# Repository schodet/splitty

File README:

Splitty
=======

This is a split ergonomic keyboard based on the Ergodox layout without the
thumb cluster. It uses 32 keys per sides with Cherry MX compatibles switches,
thirty 1u and two vertical 1.5u caps.

The controller is integrated in order to make the keyboard as slim as
possible.

It connects to the computer using a micro-B USB. Both sides are connected
together also using micro-B USB. Any connection mistake should not break
anything and the keyboard supports hot plugging.

License
------- 

Copyright (C) 2018 Nicolas Schodet

Permission is hereby granted, free of charge, to any person obtaining a copy
of this software and associated documentation files (the "Software"), to deal
in the Software without restriction, including without limitation the rights
to use, copy, modify, merge, publish, distribute, sublicense, and/or sell
copies of the Software, and to permit persons to whom the Software is
furnished to do so, subject to the following conditions:

The above copyright notice and this permission notice shall be included in all
copies or substantial portions of the Software.

THE SOFTWARE IS PROVIDED "AS IS", WITHOUT WARRANTY OF ANY KIND, EXPRESS OR
IMPLIED, INCLUDING BUT NOT LIMITED TO THE WARRANTIES OF MERCHANTABILITY,
FITNESS FOR A PARTICULAR PURPOSE AND NONINFRINGEMENT. IN NO EVENT SHALL THE
AUTHORS OR COPYRIGHT HOLDERS BE LIABLE FOR ANY CLAIM, DAMAGES OR OTHER
LIABILITY, WHETHER IN AN ACTION OF CONTRACT, TORT OR OTHERWISE, ARISING FROM,
OUT OF OR IN CONNECTION WITH THE SOFTWARE OR THE USE OR OTHER DEALINGS IN THE
SOFTWARE.

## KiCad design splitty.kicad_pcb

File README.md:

Splitty
=======

[More pictures](gallery.md)

This is a split ergonomic keyboard based on the Ergodox layout without the
thumb cluster. It uses 32 keys per sides with Cherry MX compatibles switches,
thirty 1u and two vertical 1.5u caps.

The controller is integrated in order to make the keyboard as slim as
possible.

It connects to the computer using a micro-B USB. Both sides are connected
together also using micro-B USB. Any connection mistake should not break
anything and the keyboard supports hot plugging.

BOM
---

All prices in euro.

Here is what is needed for one half, with references at Farnell and LCSC for
some parts.

| Quantity | Designator   | Description                              | Farnell   | Price | Total | LCSC    | Price  | Total |
| -------: | ------------ | ---------------------------------------- | --------: | ----: | ----: | ------: | -----: | ----: |
|       32 | SW0-38       | Cherry MX switches                       |           |       |       |         |        |       |
|        3 | C1, C11, C12 | Capacitor 0603 1μF >6V X7R               |   2346895 | 0.055 | 0.165 |  C93816 | 0.0172 | 0.052 |
|        2 | C3, C4       | Capacitor 0603 22pF >6V C0G/NP0          |   xxxxxxx | xxxxx | xxxxx | C106245 | 0.0084 | 0.017 |
|        6 | C5-10        | Capacitor 0603 100nF >6V X7R             |   2320803 | 0.037 | 0.222 | C187860 | 0.0231 | 0.139 |
|       32 | D0-38        | Diode SOD-123                            |   2760402 | 0.079 | 2.528 |  C83528 | 0.0091 | 0.291 |
|        2 | J1,J2        | Connector USB Micro-B Würth 629105150521 |   2470822 | 1.360 | 2.720 |         |        |       |
|        2 | R1, R2       | Resistor 0603 22Ω                        |   9331891 | 0.002 | 0.004 |         |        |       |
|        3 | R3, R4, R5   | Resistor 0603 10kΩ                       |   xxxxxxx | xxxxx | xxxxx |         |        |       |
|        1 | SW40         | Tactile Switches Omron B3U-3000P-B       |   1333656 | 0.420 | 0.420 |         |        |       |
|        1 | U1           | ATmega32U4-AU                            |   2443182 | 3.570 | 3.570 |  C44854 | 3.1513 | 3.151 |
|        2 | U2, U3       | ST USBLC6-2SC6                           |   1269406 | 0.313 | 0.626 |   C7519 | 0.1456 | 0.291 |
|        1 | Y1           | Crystal Abracon ABM3 16MHz               |   1611806 | 0.660 | 0.660 |         |        |       |
|        8 |              | M2 screw, 6mm                            |   1420386 | 0.012 | 0.094 |         |        |       |
|       16 |              | M2 nuts                                  |   1419445 | 0.009 | 0.150 |         |        |       |
|          |              |                                          |           | Total | 11.19 |         |        |       |
|          |              |                                          |           |    x2 | 22.38 |         |        |       |

Boards were ordered at JLCPCB, you can ask for delivery of JLCPCB and LCSC
orders in the same package.

| Description                   | JLCPCB by | Price | Unit  | JLCPCB by | Price | Unit  |
| ----------------------------- | --------- | ----- | ----- | --------- | ----- | ----- |
| Printed Circuit Board (green) |         5 | 11.25 | 2.250 |        10 | 15.20 | 1.520 |
| Front Plate (white)           |         5 | 18.55 | 3.710 |        10 | 22.49 | 2.249 |
| Back Plate (white)            |         5 | 18.55 | 3.710 |        10 | 22.49 | 2.249 |

My actual orders
----------------

Cool Jazz (AliExpress):

 - 92 Gateron MX brown switches: 21.93 €
 - Ergodox PBT blank keycaps (60 1u, 16 1.5u, 4 2u): 23.12 €
 - Total: 45.05 €

Farnell:

 - 4 connector USB: 5.44 €
 - 2 quartz: 1.32 €
 - 100 screws: 1.17 €
 - 100 nuts: 0.94 €
 - Shipping: 6.90 €
 - Taxes: 3.16 €
 - Total: 18.93 €

JLCPCB + LCSC:

 - 5 PCB: 11.25 €
 - 5 Front Plate: 18.55 €
 - 5 Back Plate: 18.55 €
 - Shipping (JLCPCB, DHL): 5.03 €
 - 10 ST USBLC6: 0.72 €
 - 4 ATmega32U4: 12.59 €
 - 140 diodes: 1.27 €
 - 50 1uF capacitors: 0.86 €
 - Shipping (LCSC): 0.17 €
 - Taxes + DHL tip(!): 27 €
 - Total: 95.99 €

Personal stock:
 - Some resistors and capacitors.

I have enough components for two keyboards except USB connectors, quartz
(forgotten in Farnell order), switches and caps (they will probably be
different), and an extra set of boards.

Grand total: 159.97 €

Grand total (for one keyboard): 111.98 €

Slim stack
----------

A special attachment is used to make sure the stack is as slim as possible:

Assembly and more
-----------------

See the [build log](build.md) and the [FAQ](faq.md).

License
-------

Copyright (C) 2018 Nicolas Schodet

Permission is hereby granted, free of charge, to any person obtaining a copy
of this software and associated documentation files (the "Software"), to deal
in the Software without restriction, including without limitation the rights
to use, copy, modify, merge, publish, distribute, sublicense, and/or sell
copies of the Software, and to permit persons to whom the Software is
furnished to do so, subject to the following conditions:

The above copyright notice and this permission notice shall be included in all
copies or substantial portions of the Software.

THE SOFTWARE IS PROVIDED "AS IS", WITHOUT WARRANTY OF ANY KIND, EXPRESS OR
IMPLIED, INCLUDING BUT NOT LIMITED TO THE WARRANTIES OF MERCHANTABILITY,
FITNESS FOR A PARTICULAR PURPOSE AND NONINFRINGEMENT. IN NO EVENT SHALL THE
AUTHORS OR COPYRIGHT HOLDERS BE LIABLE FOR ANY CLAIM, DAMAGES OR OTHER
LIABILITY, WHETHER IN AN ACTION OF CONTRACT, TORT OR OTHERWISE, ARISING FROM,
OUT OF OR IN CONNECTION WITH THE SOFTWARE OR THE USE OR OTHER DEALINGS IN THE
SOFTWARE.

The splitty symbol and footprint libraries use the same license.

Artwork on the back plate was made from "Van Volkswagen Vintage Old Car
Transporter Vw" under Creative Commons Zero - CC0.

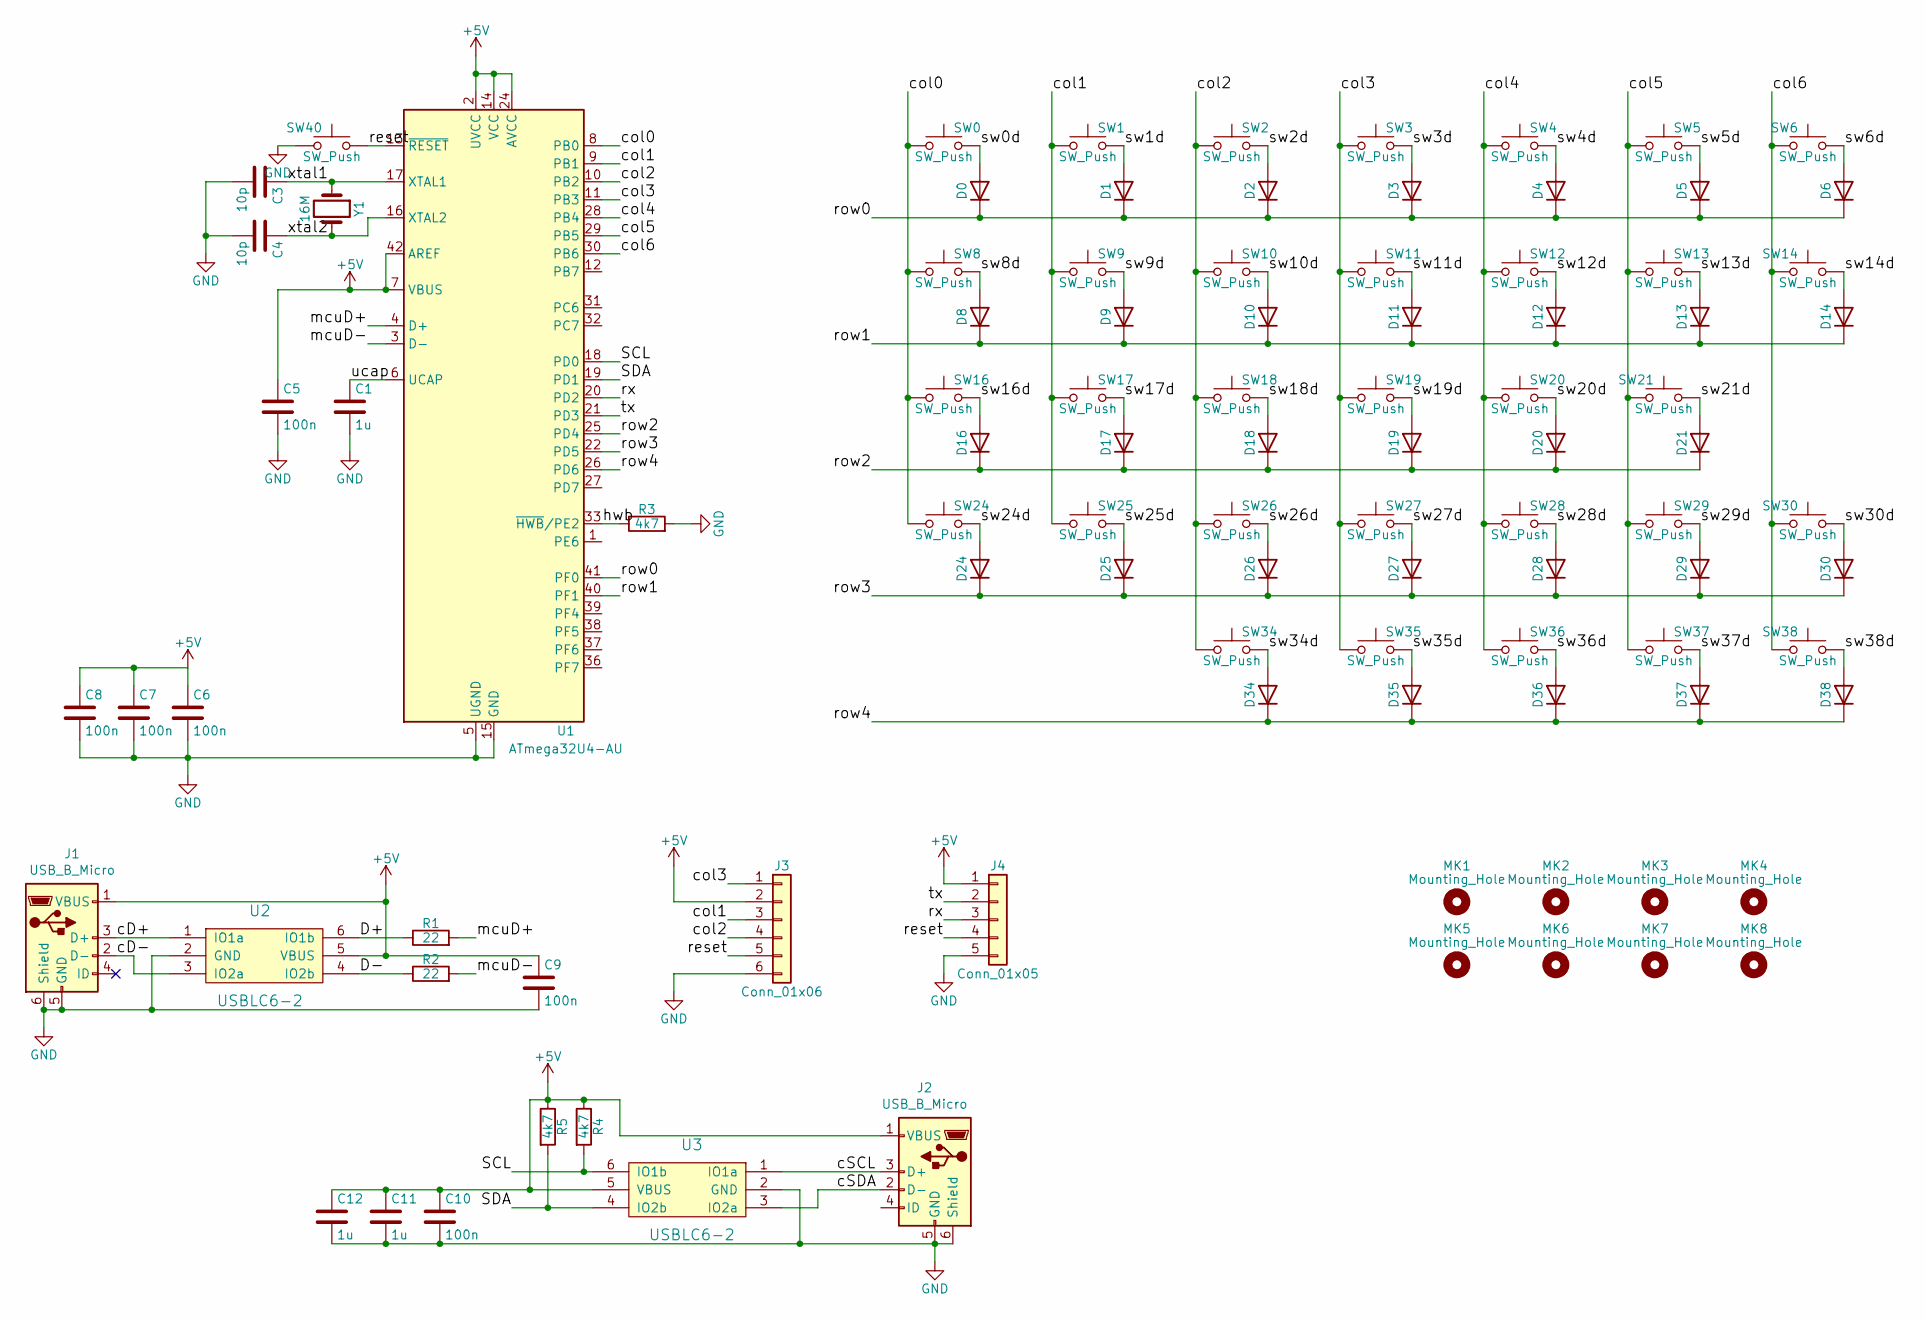
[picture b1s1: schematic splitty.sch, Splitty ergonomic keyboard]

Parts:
C1, C11, C12: 1u; C_0603_1608Metric_Pad1.05x0.95mm_HandSolder
C3, C4: 10p; C_0603_1608Metric_Pad1.05x0.95mm_HandSolder
C5, C6, C7, C8, C9, C10: 100n; C_0603_1608Metric_Pad1.05x0.95mm_HandSolder
D0, D1, D2, D3, D4, D5, D6, D8, D9, D10, D11, D12, D13, D14, D16, D17, D18, D19, D20, D21, D24, D25, D26, D27, D28, D29, D30, D34, D35, D36, D37, D38: D; D_SOD-123_BothSides
J1, J2: USB_B_Micro; USB_Micro-B_Wuerth_629105150521_BothSides
J3: Conn_01x06; PinHeader_1x06_P2.54mm_Vertical
J4: Conn_01x05; PinHeader_1x05_P2.54mm_Vertical
MK1, MK2, MK3, MK4, MK5, MK6, MK7, MK8: Mounting_Hole; MountingHole_2.2mm_M2
R1, R2: 22; R_0603_1608Metric_Pad1.05x0.95mm_HandSolder
R3, R4, R5: 4k7; R_0603_1608Metric_Pad1.05x0.95mm_HandSolder
SW0, SW1, SW2, SW3, SW4, SW5, SW6, SW8, SW9, SW10, SW11, SW12, SW13, SW16, SW17, SW18, SW19, SW20, SW21, SW24, SW25, SW26, SW27, SW28, SW29, SW34, SW35, SW36, SW37, SW38: SW_Push; SW_Cherry_MX1A_1.00u_PCB_BothSides
SW14, SW30: SW_Push; SW_Cherry_MX1A_1.50u_PCB_BothSides
SW40: SW_Push; Tact_Switch_Side_Boss_B3U-3000P-B_BothSides_HandSolder
U1: ATmega32U4-AU; TQFP-44_10x10mm_P0.8mm
U2, U3: USBLC6-2; SOT-23-6_Handsoldering
Y1: 16M; Crystal_SMD_Abracon_ABM3-2Pin_5.0x3.2mm_HandSoldering

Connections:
+5V: C5.1, C6.1, C7.1, C8.1, C9.1, C10.1, C11.1, C12.1, J1.1 (VBUS), J2.1 (VBUS), J3.2, J4.1, R4.1, R5.1, U1.2 (UVCC), U1.7 (VBUS), U1.14 (VCC), U1.24 (AVCC), U1.34 (VCC), U1.42 (AREF), U1.44 (AVCC), U2.5 (VBUS), U3.5 (VBUS)
/D+: R1.1, U2.6 (IO1b)
/D-: R2.1, U2.4 (IO2b)
/SCL: R4.2, U1.18 (PD0), U3.6 (IO1b)
/SDA: R5.2, U1.19 (PD1), U3.4 (IO2b)
/cD+: J1.3 (D+), U2.1 (IO1a)
/cD-: J1.2 (D-), U2.3 (IO2a)
/cSCL: J2.3 (D+), U3.1 (IO1a)
/cSDA: J2.2 (D-), U3.3 (IO2a)
/col0: SW0.1, SW8.1, SW16.1, SW24.1, U1.8 (PB0)
/col1: J3.3, SW1.1, SW9.1, SW17.1, SW25.1, U1.9 (PB1)
/col2: J3.4, SW2.1, SW10.1, SW18.1, SW26.1, SW34.1, U1.10 (PB2)
/col3: J3.1, SW3.1, SW11.1, SW19.1, SW27.1, SW35.1, U1.11 (PB3)
/col4: SW4.1, SW12.1, SW20.1, SW28.1, SW36.1, U1.28 (PB4)
/col5: SW5.1, SW13.1, SW21.2, SW29.1, SW37.1, U1.29 (PB5)
/col6: SW6.2, SW14.2, SW30.2, SW38.2, U1.30 (PB6)
/hwb: R3.1, U1.33 (~HWB~/PE2)
/mcuD+: R1.2, U1.4 (D+)
/mcuD-: R2.2, U1.3 (D-)
/reset: J3.5, J4.4, SW40.1, U1.13 (~RESET)
/row0: D0.1 (K), D1.1 (K), D2.1 (K), D3.1 (K), D4.1 (K), D5.1 (K), D6.1 (K), U1.41 (PF0)
/row1: D8.1 (K), D9.1 (K), D10.1 (K), D11.1 (K), D12.1 (K), D13.1 (K), D14.1 (K), U1.40 (PF1)
/row2: D16.1 (K), D17.1 (K), D18.1 (K), D19.1 (K), D20.1 (K), D21.1 (K), U1.25 (PD4)
/row3: D24.1 (K), D25.1 (K), D26.1 (K), D27.1 (K), D28.1 (K), D29.1 (K), D30.1 (K), U1.22 (PD5)
/row4: D34.1 (K), D35.1 (K), D36.1 (K), D37.1 (K), D38.1 (K), U1.26 (PD6)
/rx: J4.3, U1.20 (PD2)
/sw0d: D0.2 (A), SW0.2
/sw1d: D1.2 (A), SW1.2
/sw2d: D2.2 (A), SW2.2
/sw3d: D3.2 (A), SW3.2
/sw4d: D4.2 (A), SW4.2
/sw5d: D5.2 (A), SW5.2
/sw6d: D6.2 (A), SW6.1
/sw8d: D8.2 (A), SW8.2
/sw9d: D9.2 (A), SW9.2
/sw10d: D10.2 (A), SW10.2
/sw11d: D11.2 (A), SW11.2
/sw12d: D12.2 (A), SW12.2
/sw13d: D13.2 (A), SW13.2
/sw14d: D14.2 (A), SW14.1
/sw16d: D16.2 (A), SW16.2
/sw17d: D17.2 (A), SW17.2
/sw18d: D18.2 (A), SW18.2
/sw19d: D19.2 (A), SW19.2
/sw20d: D20.2 (A), SW20.2
/sw21d: D21.2 (A), SW21.1
/sw24d: D24.2 (A), SW24.2
/sw25d: D25.2 (A), SW25.2
/sw26d: D26.2 (A), SW26.2
/sw27d: D27.2 (A), SW27.2
/sw28d: D28.2 (A), SW28.2
/sw29d: D29.2 (A), SW29.2
/sw30d: D30.2 (A), SW30.1
/sw34d: D34.2 (A), SW34.2
/sw35d: D35.2 (A), SW35.2
/sw36d: D36.2 (A), SW36.2
/sw37d: D37.2 (A), SW37.2
/sw38d: D38.2 (A), SW38.1
/tx: J4.2, U1.21 (PD3)
/ucap: C1.1, U1.6 (UCAP)
/xtal1: C3.1, U1.17 (XTAL1), Y1.1
/xtal2: C4.1, U1.16 (XTAL2), Y1.2
GND: C1.2, C3.2, C4.2, C5.2, C6.2, C7.2, C8.2, C9.2, C10.2, C11.2, C12.2, J1.5 (GND), J1.6 (Shield), J2.5 (GND), J2.6 (Shield), J3.6, J4.5, R3.2, SW40.2, U1.5 (UGND), U1.15 (GND), U1.23 (GND), U1.35 (GND), U1.43 (GND), U2.2 (GND), U3.2 (GND)

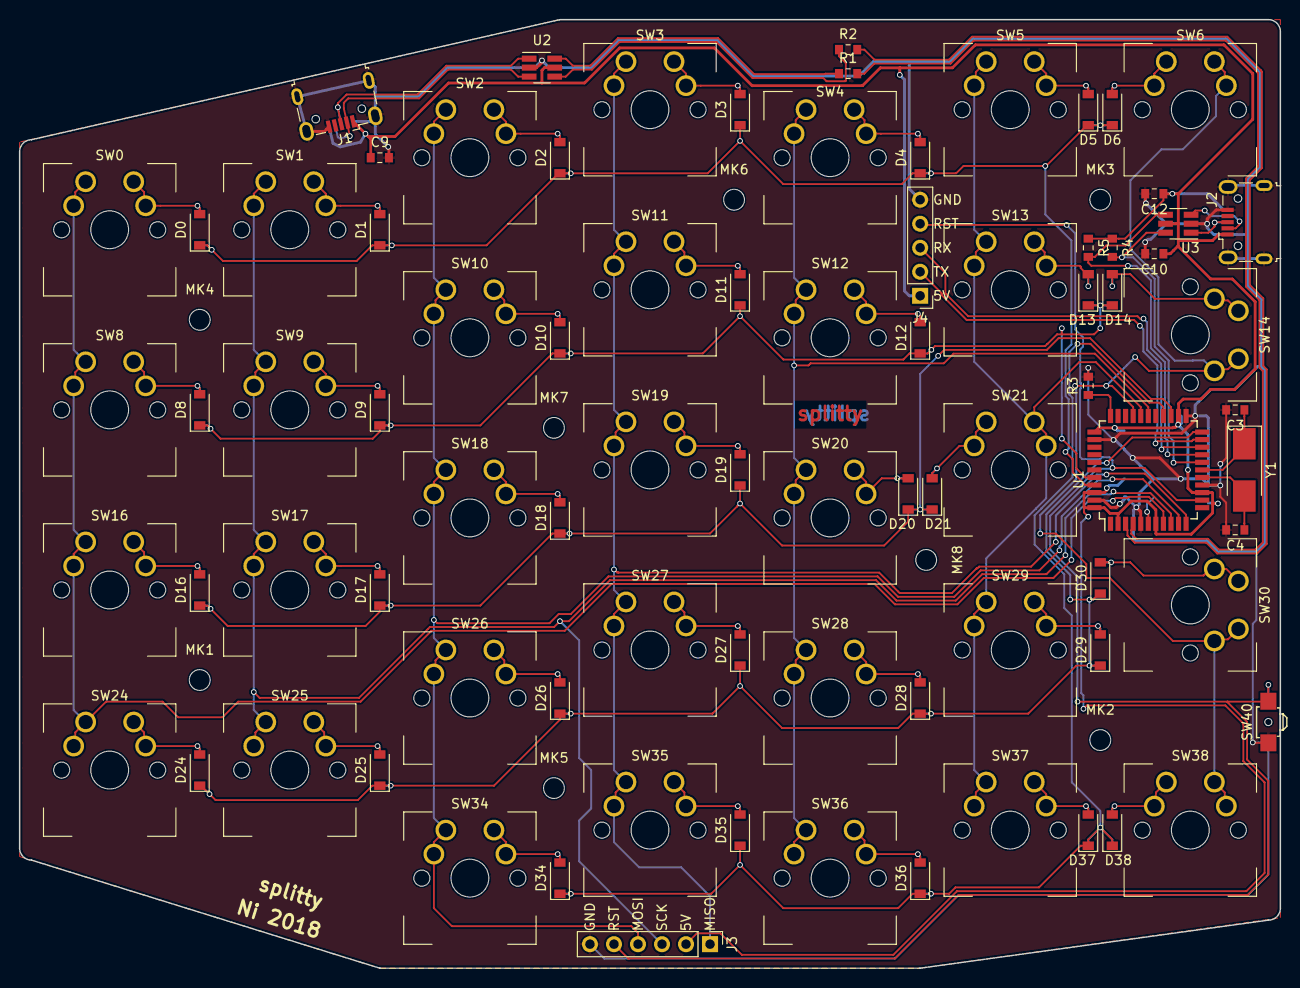
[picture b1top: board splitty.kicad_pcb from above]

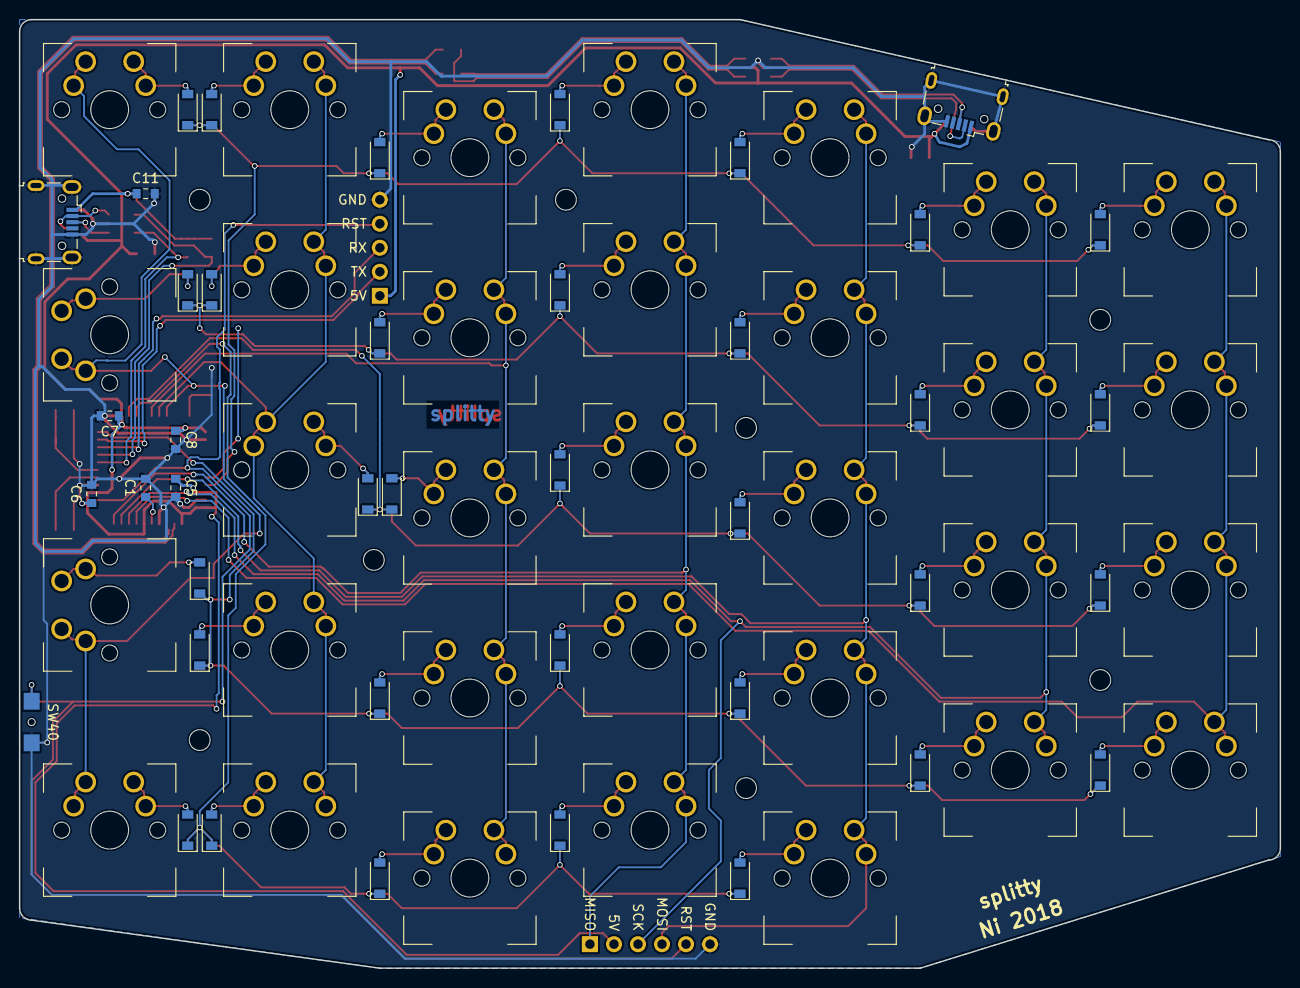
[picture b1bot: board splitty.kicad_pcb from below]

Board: 2 copper layers, 133.4 x 100.3 mm, 97 parts (6 on the bottom side), 63 nets.

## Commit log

2018-05-26 First release, full schematic and routed board
2018-05-26 Add front & back plates
2018-05-27 Add drawing to backplate
2018-05-27 Add some LCSC references
2018-05-27 Change README extension
2018-06-16 Update bom and README
2018-06-30 Add build log and gallery
2018-07-01 Add FAQ
2018-07-15 Add file for Bépo for keyboard-layout-editor.com
2018-07-16 KLE fix for Bépo layout
2018-09-10 Update to Kicad 5
2020-01-09 BOM update
2020-01-09 Update KLE layout
2021-02-07 Add more copyright and license info, upgrade Kicad
2021-02-07 Add schematic as PDF and fabrication files
2021-02-08 Add separated LICENSE file

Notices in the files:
splitty.kicad_pcb:
License: MIT
Copyright © 2018 Nicolas Schodet
